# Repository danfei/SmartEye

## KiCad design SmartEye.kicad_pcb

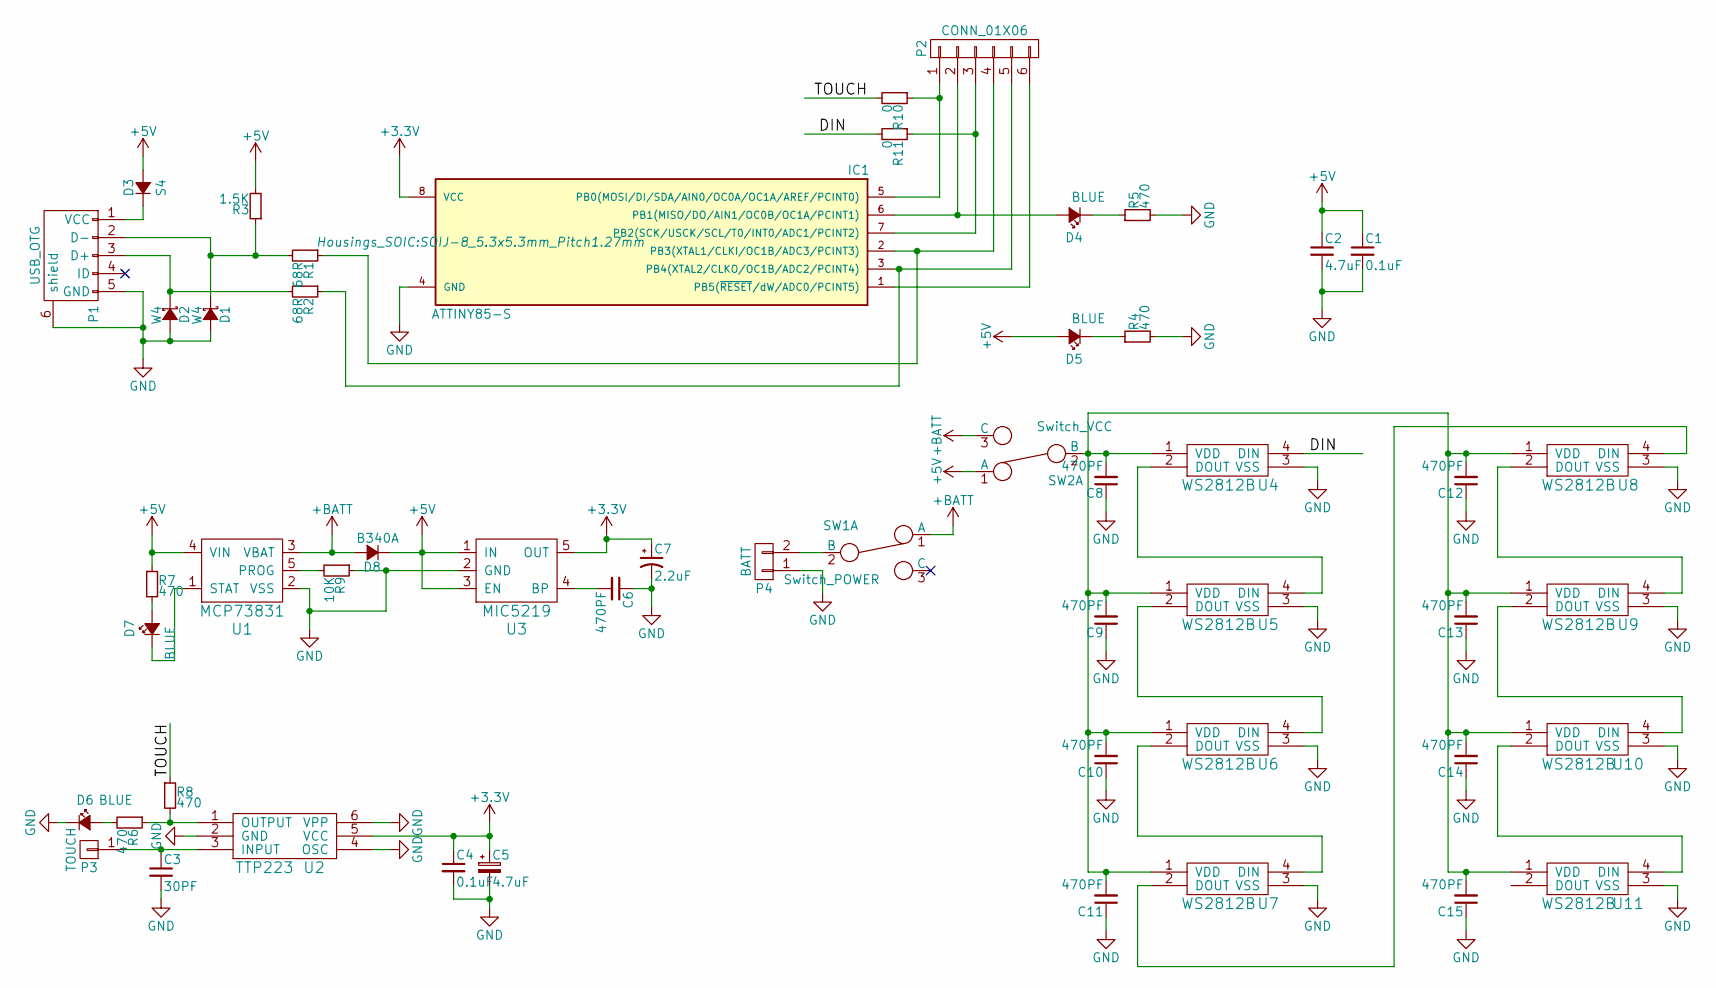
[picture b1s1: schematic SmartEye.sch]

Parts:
C1, C4: 0.1uF; C_0603_HandSoldering
C2: 4.7uF; C_0603_HandSoldering
C3: 30PF; C_0603_HandSoldering
C5: 4.7uF; TantalC_SizeA_EIA-3216_HandSoldering
C6, C8, C9, C10, C11, C12, C13, C14, C15: 470PF; C_0603_HandSoldering
C7: 2.2uF; TantalC_SizeA_EIA-3216_HandSoldering
D1, D2: W4; SOD-123
D3: S4; SOD-123
D4, D5, D6, D7: BLUE; LED_0603
D8: B340A; SOD-123
IC1: ATTINY85-S; SOIJ-8_5.3x5.3mm_Pitch1.27mm
P1: USB_OTG; USB_Micro-B
P2: CONN_01X06; Pin_Header_Straight_1x06
P3: TOUCH
P4: BATT; CR2477
R1, R2: 68R; R_0603_HandSoldering
R3: 1.5K; R_0603_HandSoldering
R4, R5, R6, R7, R8: 470; R_0603_HandSoldering
R9: 10K; R_0603_HandSoldering
R10, R11: 0; R_0603_HandSoldering
SW1: Switch_POWER; SW_SPDT_PCM12
SW2: Switch_VCC; SW_SPDT_PCM12
U1: MCP73831; SOT-23-5
U2: TTP223; SOT-23-6
U3: MIC5219; SOT-23-5
U4, U5, U6, U7, U8, U9, U10, U11: WS2812B; LED_WS2812B-PLCC4

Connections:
+3V3: C4.1, C5.1, C7.1, IC1.8 (VCC), U2.5 (VCC), U3.5 (OUT)
+5V: C1.1, C2.1, D3.2 (A), D5.2 (A), D8.1 (K), R3.2, R7.1, SW2.1 (A), U1.4 (VIN), U3.1 (IN), U3.3 (EN)
+BATT: D8.2 (A), SW1.1 (A), SW2.3 (C), U1.3 (VBAT)
/DIN: R11.2, U4.4 (DIN)
/TOUCH: R8.1, R10.2
GND: C1.2, C2.2, C3.2, C4.2, C5.2, C6.1, C7.2, C8.1, C9.1, C10.1, C11.1, C12.1, C13.1, C14.1, C15.1, D1.2 (A), D2.2 (A), D6.1 (K), IC1.4 (GND), P1.5 (GND), P1.6 (shield), P4.1, R4.2, R5.2, R9.1, U1.2 (VSS), U2.2 (GND), U2.4 (OSC), U2.6 (VPP), U3.2 (GND), U4.3 (VSS), U5.3 (VSS), U6.3 (VSS), U7.3 (VSS), U8.3 (VSS), U9.3 (VSS), U10.3 (VSS), U11.3 (VSS)
unnamed: C3.1, P3.1, U2.3 (INPUT)
unnamed: C6.2, U3.4 (BP)
unnamed: C8.2, C9.2, C10.2, C11.2, C12.2, C13.2, C14.2, C15.2, SW2.2 (B), U4.1 (VDD), U5.1 (VDD), U6.1 (VDD), U7.1 (VDD), U8.1 (VDD), U9.1 (VDD), U10.1 (VDD), U11.1 (VDD)
unnamed: D1.1 (K), P1.2 (D-), R1.2, R3.1
unnamed: D2.1 (K), P1.3 (D+), R2.2
unnamed: D3.1 (K), P1.1 (VCC)
unnamed: D4.1 (K), R5.1
unnamed: D4.2 (A), IC1.6 (PB1(MISO/DO/AIN1/OC0B/OC1A/PCINT1)), P2.2
unnamed: D5.1 (K), R4.1
unnamed: D6.2 (A), R6.2
unnamed: D7.1 (K), U1.1 (STAT)
unnamed: D7.2 (A), R7.2
unnamed: IC1.1 (PB5(~RESET~/dW/ADC0/PCINT5)), P2.6
unnamed: IC1.2 (PB3(XTAL1/CLKI/OC1B/ADC3/PCINT3)), P2.4, R1.1
unnamed: IC1.3 (PB4(XTAL2/CLKO/OC1B/ADC2/PCINT4)), P2.5, R2.1
unnamed: IC1.5 (PB0(MOSI/DI/SDA/AIN0/OC0A/OC1A/AREF/PCI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), P2.1, R10.1
unnamed: IC1.7 (PB2(SCK/USCK/SCL/T0/INT0/ADC1/PCINT2)), P2.3, R11.1
unnamed: P4.2, SW1.2 (B)
unnamed: R6.1, R8.2, U2.1 (OUTPUT)
unnamed: R9.2, U1.5 (PROG)
unnamed: U4.2 (DOUT), U5.4 (DIN)
unnamed: U5.2 (DOUT), U6.4 (DIN)
unnamed: U6.2 (DOUT), U7.4 (DIN)
unnamed: U7.2 (DOUT), U8.4 (DIN)
unnamed: U8.2 (DOUT), U9.4 (DIN)
unnamed: U10.2 (DOUT), U11.4 (DIN)
unnamed: U9.2 (DOUT), U10.4 (DIN)

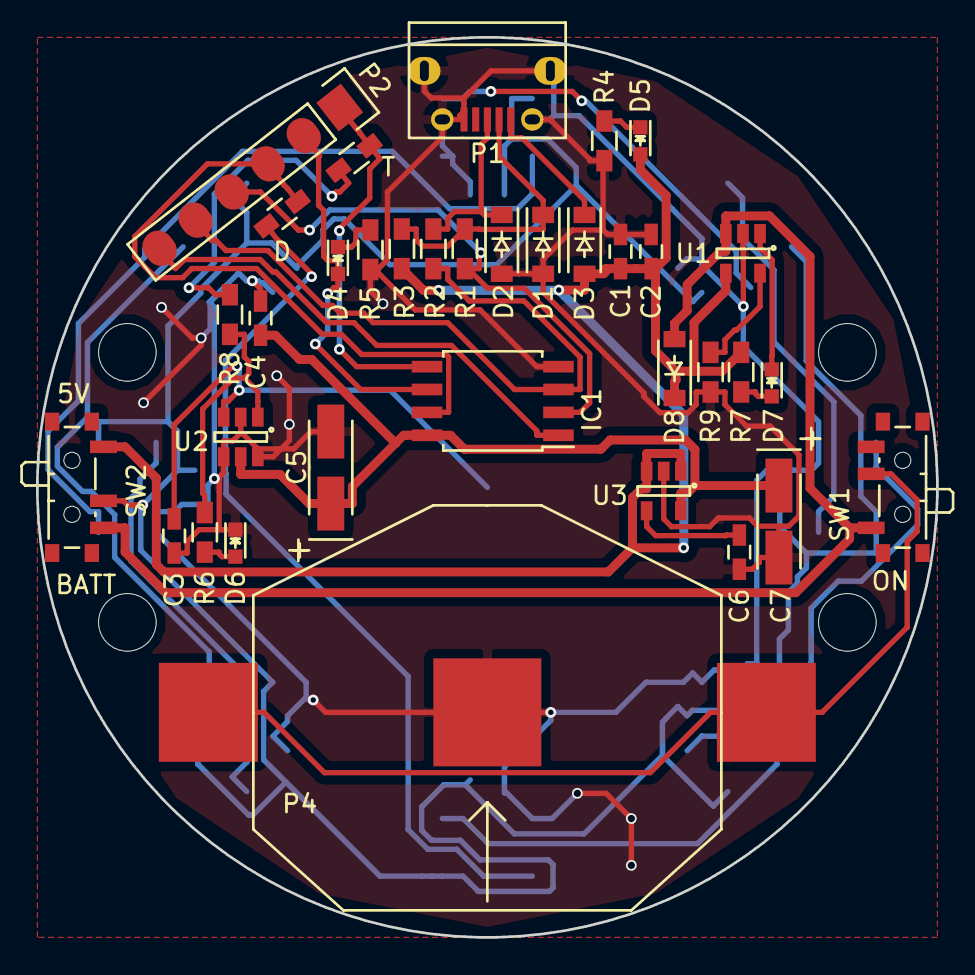
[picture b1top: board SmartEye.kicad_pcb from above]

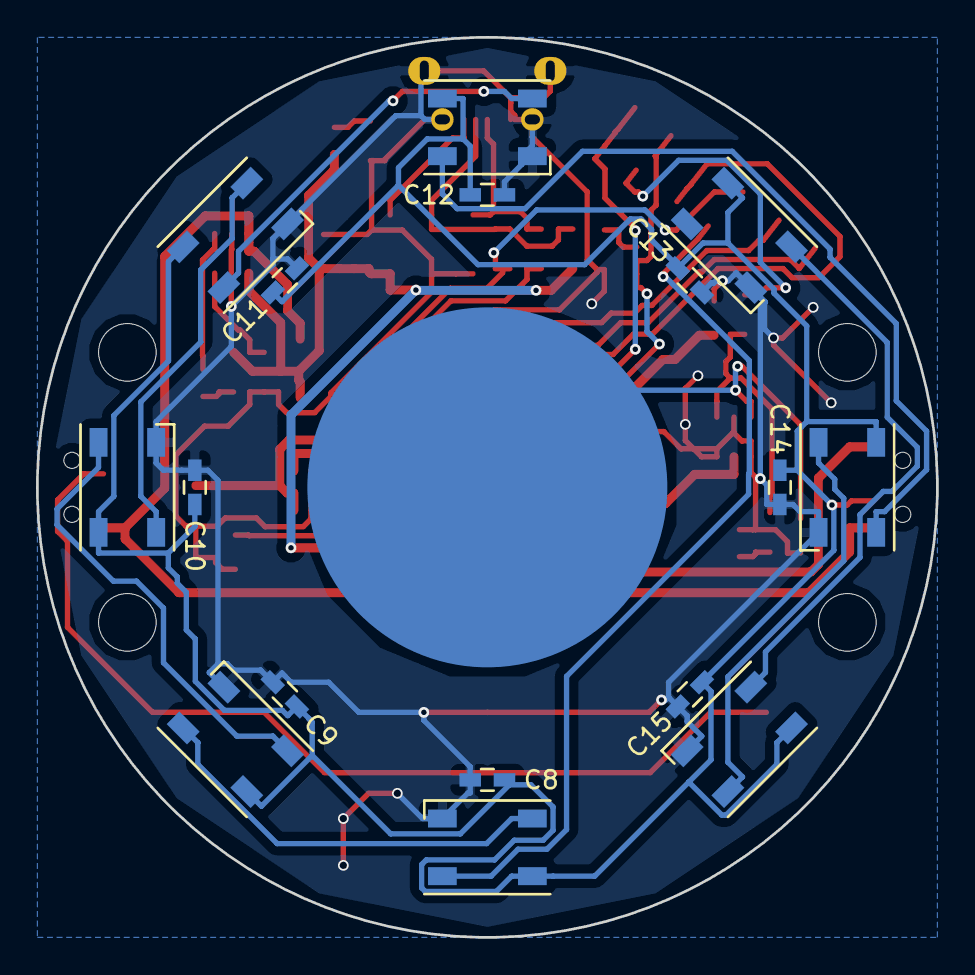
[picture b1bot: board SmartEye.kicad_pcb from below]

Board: 2 copper layers, 50.0 x 50.0 mm, 56 parts (17 on the bottom side), 33 nets.

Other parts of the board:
REF1, REF2, REF3, REF4: MountingHole_3.2mm_M3

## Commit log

2016-12-23 Alpha version
